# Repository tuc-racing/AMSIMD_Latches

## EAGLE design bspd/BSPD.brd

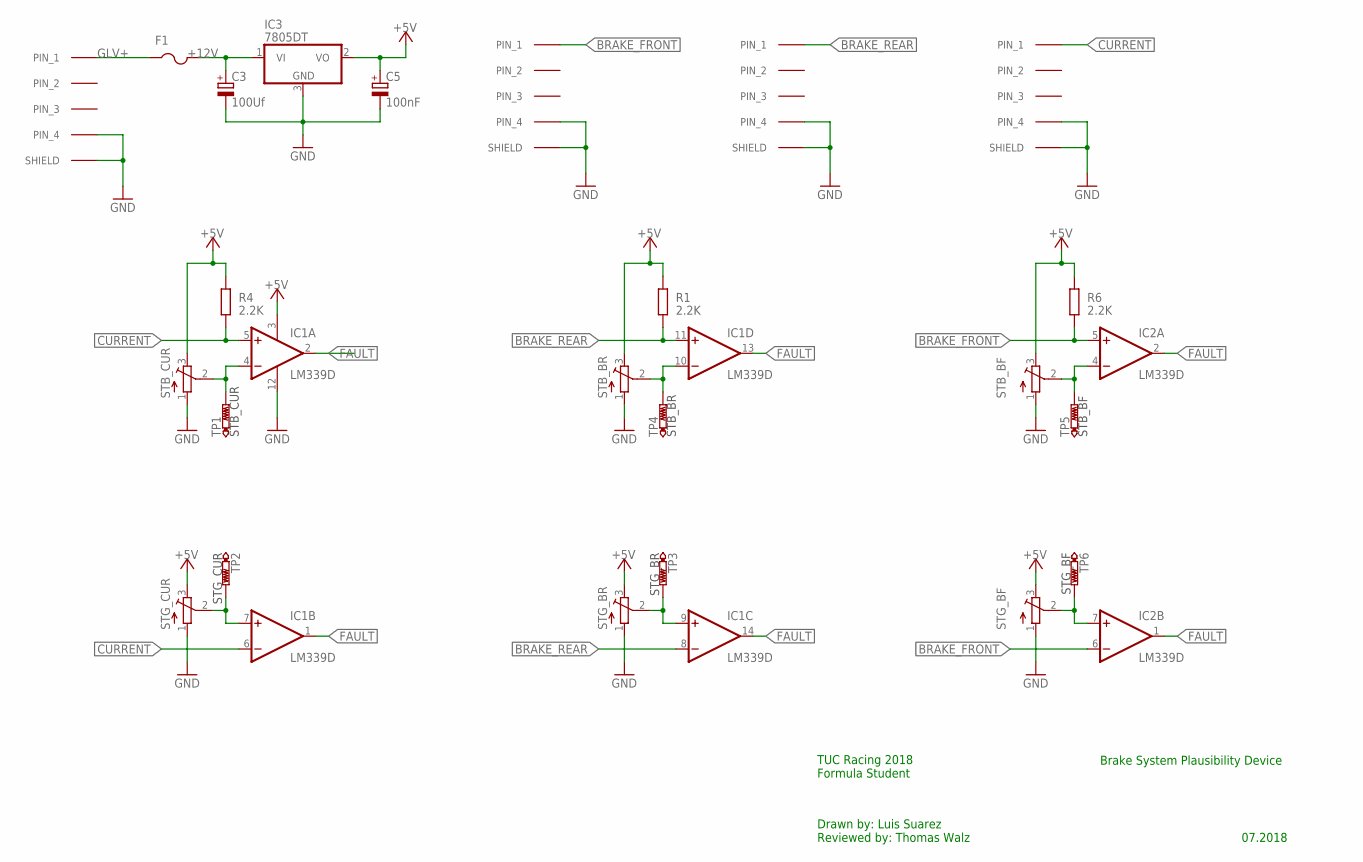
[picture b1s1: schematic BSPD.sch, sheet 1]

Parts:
C3: 100Uf; PANASONIC_D
C5: 100nF; PANASONIC_C
F1: PTCFUSE-1206; R1206
IC1, IC2: LM339D; SO14
IC3: 7805DT; TO252
POWER, POWER1, POWER2, POWER3: M8-718-MALE; M18-718-MALE
R1, R4, R6: 2.2K; R0805
STB_BF: TRIM_EU-SM-42/43B; SM-42/43B
STB_BR: TRIM_EU-SM-42/43B; SM-42/43B
STB_CUR: TRIM_EU-SM-42/43B; SM-42/43B
STG_BF: TRIM_EU-SM-42/43B; SM-42/43B
STG_BR: TRIM_EU-SM-42/43B; SM-42/43B
STG_CUR: TRIM_EU-SM-42/43B; SM-42/43B
TP1, TP2, TP3, TP4, TP5, TP6: PTR1PAD1-13; P1-13

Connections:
+5V: C5.+, IC1.3 (V+), IC3.2 (VO), R1.2, R4.2, R6.2, STB_BF.3 (E), STB_BR.3 (E), STB_CUR.3 (E), STG_BF.3 (E), STG_BR.3 (E), STG_CUR.3 (E); also elsewhere on the board
+12V: C3.+, F1.2, IC3.1 (VI)
BRAKE_FRONT: IC2.5 (+IN), IC2.6 (-IN), POWER1.P$1 (PIN_1), R6.1
BRAKE_REAR: IC1.8 (-IN), IC1.11 (+IN), POWER2.P$1 (PIN_1), R1.1
CURRENT: IC1.5 (+IN), IC1.6 (-IN), POWER3.P$1 (PIN_1), R4.1
FAULT: IC1.1 (OUT), IC1.2 (OUT), IC1.13 (OUT), IC1.14 (OUT), IC2.1 (OUT), IC2.2 (OUT); also elsewhere on the board
GLV+: F1.1, POWER.P$1 (PIN_1); also elsewhere on the board
GND: C3.-, C5.-, IC1.12 (GND), IC3.3 (GND), POWER.L (SHIELD), POWER.P$4 (PIN_4), POWER.R (SHIELD), POWER1.L (SHIELD), POWER1.P$4 (PIN_4), POWER1.R (SHIELD), POWER2.L (SHIELD), POWER2.P$4 (PIN_4), POWER2.R (SHIELD), POWER3.L (SHIELD), POWER3.P$4 (PIN_4), POWER3.R (SHIELD), STB_BF.1 (A), STB_BR.1 (A), STB_CUR.1 (A), STG_BF.1 (A), STG_BR.1 (A), STG_CUR.1 (A); also elsewhere on the board
STB_BF_TH: IC2.4 (-IN), STB_BF.2 (S), TP5.TP
STB_BR_TH: IC1.10 (-IN), STB_BR.2 (S), TP4.TP
STB_CUR_TH: IC1.4 (-IN), STB_CUR.2 (S), TP1.TP
STG_BR_TH: IC1.9 (+IN), STG_BR.2 (S), TP3.TP
STG_CUR_TH: IC1.7 (+IN), STG_CUR.2 (S), TP2.TP
TP_STG_BF: IC2.7 (+IN), STG_BF.2 (S), TP6.TP

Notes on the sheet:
Brake System Plausibility Device
07.2018
Drawn by: Luis Suarez Reviewed by: Thomas Walz
TUC Racing 2018 Formula Student

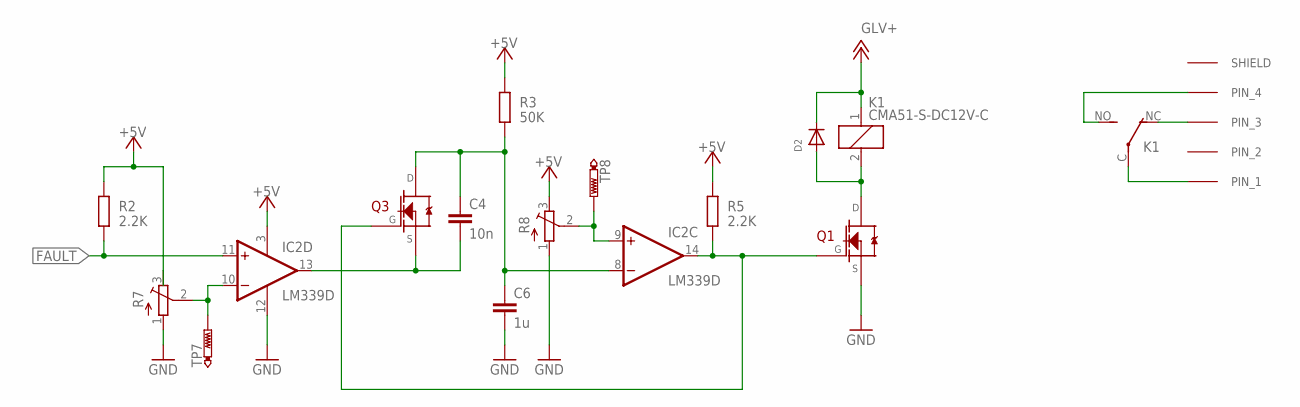
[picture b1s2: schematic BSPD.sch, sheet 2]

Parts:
C4: 10n; C1210
C6: 1u; C1210
D2: DIODESOD-123; SOD-123
IC2: LM339D; SO14
K1: CMA51-S-DC12V-C; CQ1
Q1, Q3: INF-PG-TDSON-8-1_V_1; INF-PG-TDSON-8-1_V_1PRIMARY
R2, R5: 2.2K; R0805
R3: 50K; R0805
R7, R8: TRIM_EU-SM-42/43B; SM-42/43B
TP7, TP8: PTR1PAD1-13; P1-13
U$1: M8-718-MALE; M18-718-MALE

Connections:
+5V: IC2.3 (V+), R2.2, R3.2, R5.2, R7.3 (E), R8.3 (E); also elsewhere on the board
BSPD+: K1.NO (S), U$1.P$4 (PIN_4)
BSPD-: K1.C, U$1.P$1 (PIN_1)
FAULT: IC2.11 (+IN), R2.1; also elsewhere on the board
FAULT_STATE: C4.2, IC2.13 (OUT), Q3.1 (S), Q3.2 (S), Q3.3 (S)
GLV+: D2.C, K1.1; also elsewhere on the board
GND: C6.2, IC2.12 (GND), Q1.1 (S), Q1.2 (S), Q1.3 (S), R7.1 (A), R8.1 (A); also elsewhere on the board
unnamed: D2.A, K1.2, Q1.5 (D), Q1.6 (D), Q1.7 (D), Q1.8 (D)
unnamed: K1.NC (O), U$1.P$3 (PIN_3)
unnamed: IC2.10 (-IN), R7.2 (S), TP7.TP
unnamed: IC2.9 (+IN), R8.2 (S), TP8.TP
unnamed: C4.1, C6.1, IC2.8 (-IN), Q3.5 (D), Q3.6 (D), Q3.7 (D), Q3.8 (D), R3.1
OUT_STATUS: IC2.14 (OUT), Q1.4 (G), Q3.4 (G), R5.1

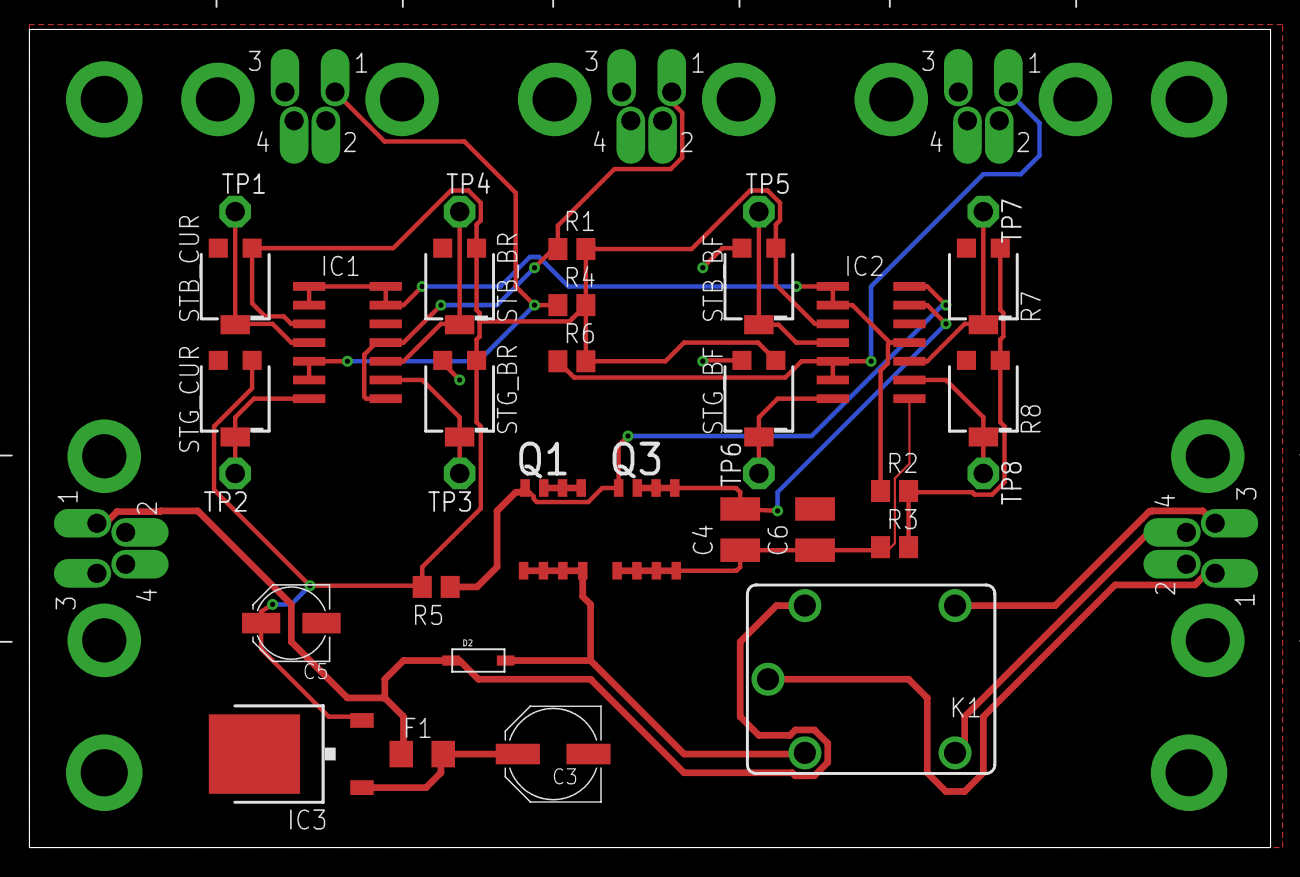
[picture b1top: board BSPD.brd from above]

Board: 2 copper layers, 84.3 x 55.5 mm, 39 parts (0 on the bottom side), 23 nets.

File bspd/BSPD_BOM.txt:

Stückliste exportiert aus C:/Users/Sean/OneDrive/Documents/T.U.C-Racing/Git_V2/hardware/bspd/BSPD.sch am 04.03.2018 19:50

Part    Value           Device               Package                     Description                                   LABEL       MF MPN OC_FARNELL OC_NEWARK TP_SIGNAL_NAME
C3      100Uf           CPOL-EUD             PANASONIC_D                 POLARIZED CAPACITOR, European symbol                                                                
C4      10n             C-EUC1210            C1210                       CAPACITOR, European symbol                                                                          
C5      100nF           CPOL-EUC             PANASONIC_C                 POLARIZED CAPACITOR, European symbol                                                                
C6      1u              C-EUC1210            C1210                       CAPACITOR, European symbol                                                                          
D2                      DIODESOD-123         SOD-123                     Diode                                                                                               
F1                      PTCFUSE-1206         R1206                       PTC fuses, resettable thermistors                                                                   
IC1     LM339D          LM339D               SO14                        Low Power Low Offset Voltage Quad Comparators                                                       
IC2     LM339D          LM339D               SO14                        Low Power Low Offset Voltage Quad Comparators                                                       
IC3     7805DT          7805DT               TO252                       Positive VOLTAGE REGULATOR                                                                          
K1      CMA51-S-DC12V-C CQ1-12V              CQ1                         AUTOMOTIVE QUIET RELAY NAiS                                      unknown    unknown                 
POWER   M8-718-MALE     M8-718-MALE          M18-718-MALE                                                              POWER                                                 
POWER1  M8-718-MALE     M8-718-MALE          M18-718-MALE                                                              BRAKE_FRONT                                           
POWER2  M8-718-MALE     M8-718-MALE          M18-718-MALE                                                              BRAKE_REAR                                            
POWER3  M8-718-MALE     M8-718-MALE          M18-718-MALE                                                              CURRENT                                               
Q1                      INF-PG-TDSON-8-1_V_1 INF-PG-TDSON-8-1_V_1PRIMARY                                                                                                     
Q3                      INF-PG-TDSON-8-1_V_1 INF-PG-TDSON-8-1_V_1PRIMARY                                                                                                     
R1      2.2K            R-EU_R0805           R0805                       RESISTOR, European symbol                                                                           
R2      2.2K            R-EU_R0805           R0805                       RESISTOR, European symbol                                                                           
R3      50K             R-EU_R0805           R0805                       RESISTOR, European symbol                                                                           
R4      2.2K            R-EU_R0805           R0805                       RESISTOR, European symbol                                                                           
R5      2.2K            R-EU_R0805           R0805                       RESISTOR, European symbol                                                                           
R6      2.2K            R-EU_R0805           R0805                       RESISTOR, European symbol                                                                           
R7                      TRIM_EU-SM-42/43B    SM-42/43B                   POTENTIOMETER                                                                                       
R8                      TRIM_EU-SM-42/43B    SM-42/43B                   POTENTIOMETER                                                                                       
STB_BF                  TRIM_EU-SM-42/43B    SM-42/43B                   POTENTIOMETER                                                                                       
STB_BR                  TRIM_EU-SM-42/43B    SM-42/43B                   POTENTIOMETER                                                                                       
STB_CUR                 TRIM_EU-SM-42/43B    SM-42/43B                   POTENTIOMETER                                                                                       
STG_BF                  TRIM_EU-SM-42/43B    SM-42/43B                   POTENTIOMETER                                                                                       
STG_BR                  TRIM_EU-SM-42/43B    SM-42/43B                   POTENTIOMETER                                                                                       
STG_CUR                 TRIM_EU-SM-42/43B    SM-42/43B                   POTENTIOMETER                                                                                       
TP1     PTR1PAD1-13     PTR1PAD1-13          P1-13                       TEST PIN                                                                              STB_CUR       
TP2     PTR1PAD1-13     PTR1PAD1-13          P1-13                       TEST PIN                                                                              STG_CUR       
TP3     PTR1PAD1-13     PTR1PAD1-13          P1-13                       TEST PIN                                                                              STG_BR        
TP4     PTR1PAD1-13     PTR1PAD1-13          P1-13                       TEST PIN                                                                              STB_BR        
TP5     PTR1PAD1-13     PTR1PAD1-13          P1-13                       TEST PIN                                                                              STB_BF        
TP6     PTR1PAD1-13     PTR1PAD1-13          P1-13                       TEST PIN                                                                              STG_BF        
TP7     PTR1PAD1-13     PTR1PAD1-13          P1-13                       TEST PIN                                                                                            
TP8     PTR1PAD1-13     PTR1PAD1-13          P1-13                       TEST PIN                                                                                            
U$1     M8-718-MALE     M8-718-MALE          M18-718-MALE                                                              OUTPUT

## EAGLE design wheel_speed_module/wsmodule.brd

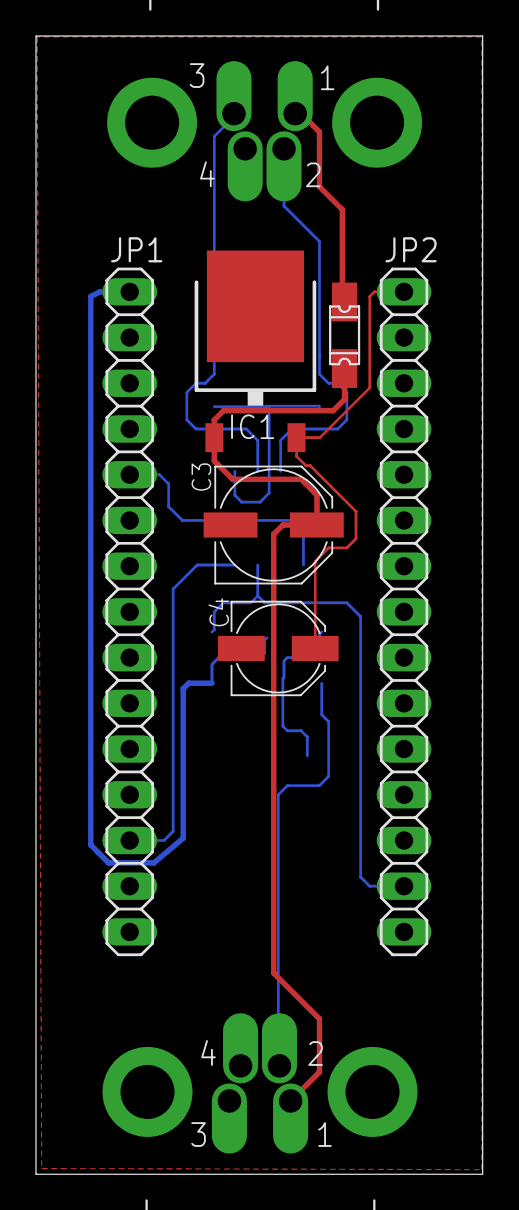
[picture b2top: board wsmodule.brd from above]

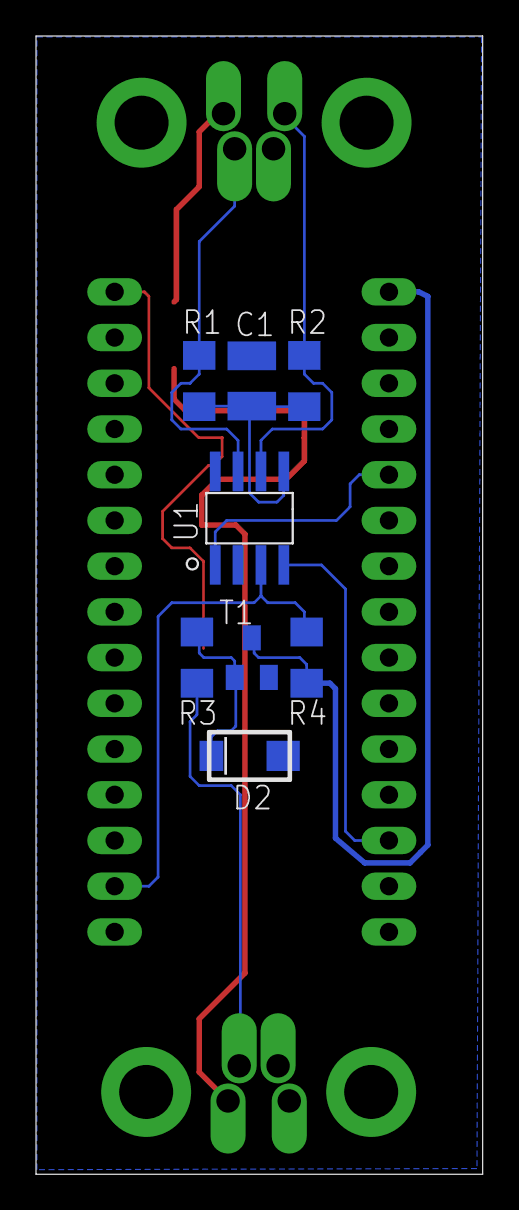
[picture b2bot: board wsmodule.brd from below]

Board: 2 copper layers, 24.8 x 63.2 mm, 16 parts (8 on the bottom side), 13 nets.

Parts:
C1: 47u; C1210
C3: 100uF; PANASONIC_D
C4: 10uF; PANASONIC_C
D2: GF1
F1: 1206L
IC1: 7805DT; TO252
INPUT: M8-718-MALE; M18-718-MALE
JP1, JP2: 1X15
OUTPUT: M8-718-FEMALE; M18-718-FEMALE
R1, R2: 60; R1206
R3, R4: 10K; R1206
T1: SOT23
U1: LTC2875XS; SO-08

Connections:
3V3: JP2.14, R4.2, U1.3
5V: C4.+, IC1.2, JP2.1
CANH: INPUT.P$2, R1.2, U1.7
CANL: INPUT.P$3, R2.2, U1.6
CAN_RX: JP1.13, U1.4
CAN_TX: JP1.5, U1.1
DIN1: JP1.1, R4.1, T1.3
GND: C1.2, C3.-, C4.-, D2.A, IC1.3, INPUT.L, INPUT.P$4, INPUT.R, JP2.2, JP2.12, OUTPUT.L, OUTPUT.P$4, OUTPUT.R, T1.2, U1.2, U1.8
HALL1: OUTPUT.P$2, R3.1
unnamed: D2.C, R3.2, T1.1
unnamed: C1.1, R1.1, R2.1, U1.5
VCC: F1.P$2, INPUT.P$1
VIN: C3.+, F1.P$1, IC1.1, OUTPUT.P$1

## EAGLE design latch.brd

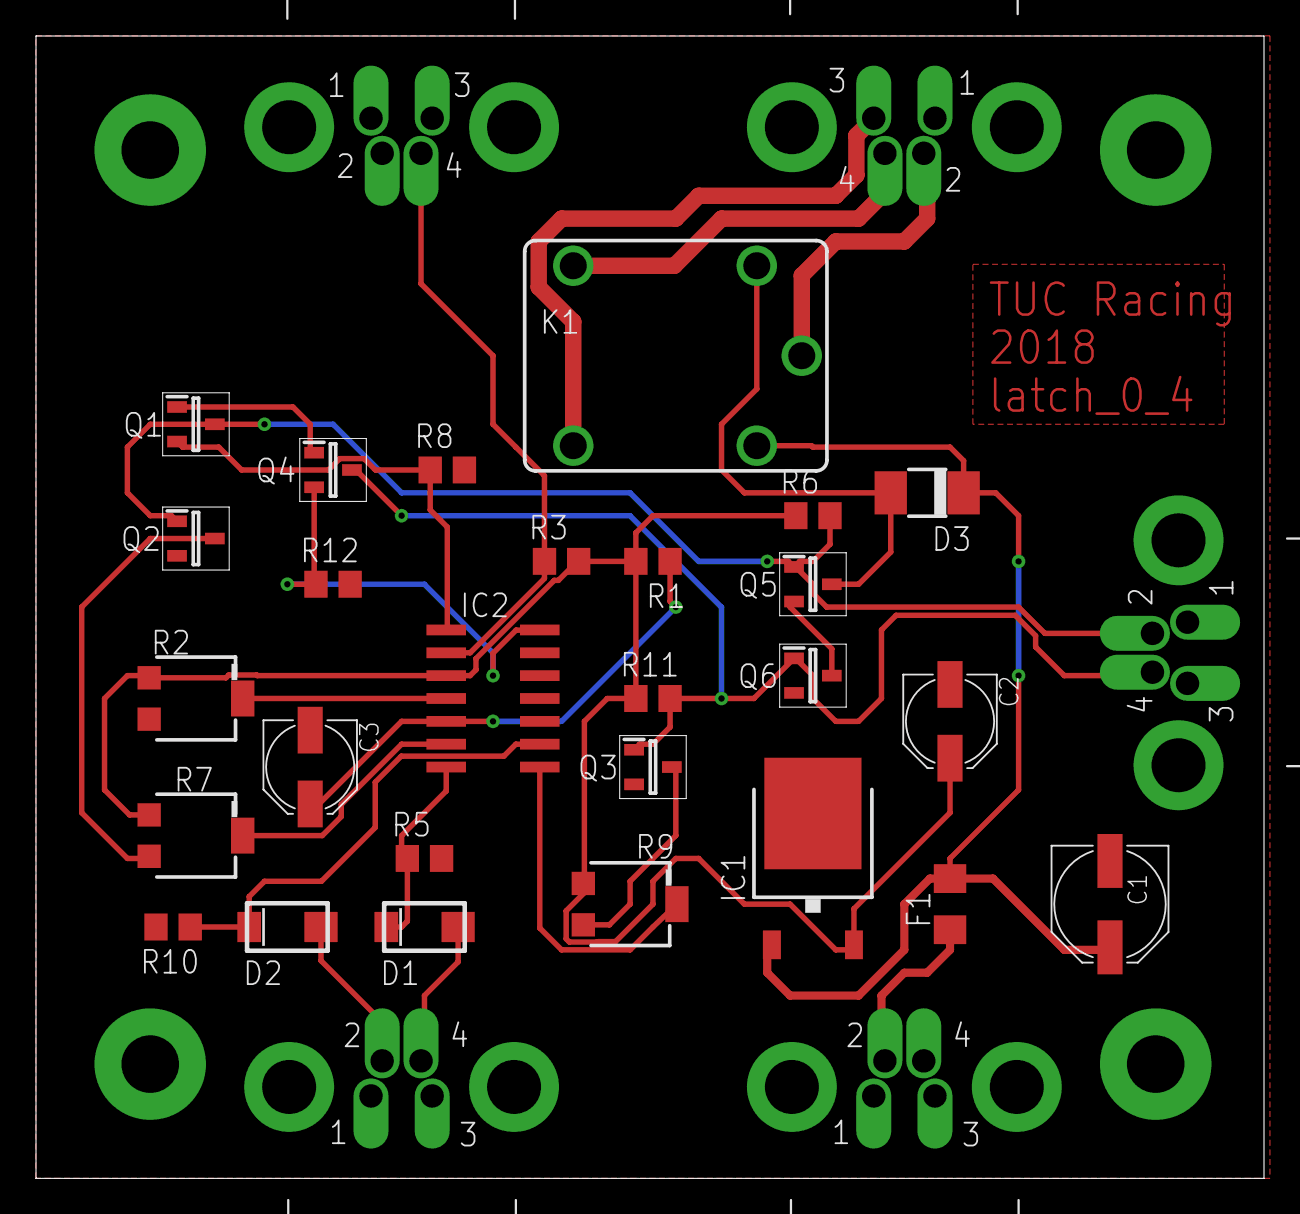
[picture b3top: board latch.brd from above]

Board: 2 copper layers, 68.2 x 63.5 mm, 32 parts (0 on the bottom side), 25 nets.

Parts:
C1: 100uF; PANASONIC_D
C2, C3: 10uF; PANASONIC_C
D1, D2: 1N4148; GF1
D3: 1N4148; DO-214AC
F1: 1A; R1206
IC1: 7805DT; TO252
IC2: LM339D; SO14
INDICATORS: M8-718-FEMALE; M18-718-FEMALE
K1: CMA51-S-DC12V-C; CQ1
LATCH: M8-718-MALE; M18-718-MALE
POWER_CONN: POWER; M18-718-MALE
Q1, Q2, Q3, Q4, Q5, Q6: BS170; SOT96P240X100-3N
R1, R8, R12: 100K; R0805
R2, R7, R9: 12K; SM-42/43B
R3, R6, R11: 1K; R0805
R5, R10: 2.2K; R0805
RESET: M8-718-FEMALE; M18-718-FEMALE
STATUS: M8-718-MALE; M18-718-MALE

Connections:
+5V: C2.+, IC1.2, IC2.3, R1.2, R2.3, R3.2, R6.2, R7.3, R9.3, R11.2
+12V: C1.+, D3.C, F1.2, IC1.1, K1.1
AMS_FAIL: INDICATORS.P$4, Q3.1, Q4.3, Q6.1, R11.1
AMS_STATUS: D2.A, STATUS.P$2
DELAY_PWR: Q1.1, Q4.1
DELAY_RESET: IC2.2, R3.1, RESET.P$4
GLV+: F1.1, POWER_CONN.P$2
GND: C1.-, C2.-, C3.-, IC1.3, IC2.10, IC2.11, IC2.12, INDICATORS.L, INDICATORS.P$1, INDICATORS.P$3, INDICATORS.R, POWER_CONN.L, POWER_CONN.P$4, POWER_CONN.R, Q2.2, Q3.2, Q6.2, R2.1, R5.1, R8.1, R10.1, R12.1, RESET.L, RESET.P$2, RESET.R, STATUS.L, STATUS.P$1, STATUS.P$3, STATUS.R
IMD_FAIL: INDICATORS.P$2, Q1.3, Q2.1, Q5.1, R6.1
IMD_STATUS: D1.A, STATUS.P$4
LATCH+: K1.NO, LATCH.P$4
LATCH-: K1.C, LATCH.P$2
unnamed: IC2.4, R2.2
unnamed: C3.+, IC2.5, R1.1
unnamed: D1.C, IC2.7, R5.2
unnamed: IC2.6, R7.2
unnamed: Q2.3, R7.1
unnamed: D2.C, IC2.9, R10.2
unnamed: IC2.1, Q1.2, R8.2
unnamed: IC2.8, R9.2
unnamed: Q3.3, R9.1
unnamed: IC2.14, Q4.2, R12.2
unnamed: D3.A, K1.2, Q5.3
unnamed: Q5.2, Q6.3
unnamed: K1.NC, LATCH.P$3

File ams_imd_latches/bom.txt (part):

Stückliste exportiert aus C:/Users/Sean/OneDrive/Documents/T.U.C-Racing/Git_V2/hardware/ams_imd_latches/latch.sch am 12.02.2018 21:47

Part       Value           Device            Package          Description                                                                                                        3D_PACKAGE ALLIED_NUMBER DESCRIPTION                                                                                                        HEIGHT MANUFACTURER_NAME MANUFACTURER_PART_NUMBER MF MPN OC_FARNELL OC_NEWARK OTHER_PART_NUMBER RS_PART_NUMBER SUPPLIER_NAME
C1         100uF           CPOL-EUD          PANASONIC_D      POLARIZED CAPACITOR, European symbol                                                                                                                                                                                                                                                                                                                                                       
C2         10uF            CPOL-EUC          PANASONIC_C      POLARIZED CAPACITOR, European symbol                                                                                                                                                                                                                                                                                                                                                       
C3         10uF            CPOL-EUC          PANASONIC_C      POLARIZED CAPACITOR, European symbol                                                                                                                                                                                                                                                                                                                                                       
D1         1N4148          DIODE-GF1         GF1              DIODE                                                                                                                                                                                                                                                                                                                                                                                      
D2         1N4148          DIODE-GF1         GF1              DIODE                                                                                                                                                                                                                                                                                                                                                                                      
D3         1N4148          DIODE-DO-214AC    DO-214AC         DIODE                                                                                                                                                                                                                                                                                                                                                                                      
F1         1A              PTCFUSE-1206      R1206            PTC fuses, resettable thermistors                                                                                                                                                                                                                                                                                                                                                          
IC1        7805DT          7805DT            TO252            Positive VOLTAGE REGULATOR                                                                                                                                                                                                                                                                                                                                                                 
IC2        LM339D          LM339D            SO14             Low Power Low Offset Voltage Quad Comparators                                                                                                                                                                                                                                                                                                                                              
INDICATORS M8-718-FEMALE   M8-718-FEMALE     M18-718-FEMALE                                                                                                                                                                                                                                                                                                                                                                                              
K1         CMA51-S-DC12V-C CQ1-12V           CQ1              AUTOMOTIVE QUIET RELAY NAiS                                                                                                                                                                                                                                                                                             unknown    unknown                                                 
LATCH      M8-718-MALE     M8-718-MALE       M18-718-MALE                                                                                                                                                                                                                                                                                                                                                                                                
POWER_CONN POWER           M8-718-MALE       M18-718-MALE                                                                                                                                                                                                                                                                                                                                                                                                
Q1         BS170           BS170FTA          SOT96P240X100-3N MOSFET N-Channel 60V 0.00015A SOT23 Diodes Inc BS170FTA N-channel MOSFET Transistor, 0.00015 A, 60 V, 3-Pin SOT-23                          MOSFET N-Channel 60V 0.00015A SOT23 Diodes Inc BS170FTA N-channel MOSFET Transistor, 0.00015 A, 60 V, 3-Pin SOT-23 1mm    Diodes Inc.       BS170FTA                                                               2156587P       RS           
Q2         BS170           BS170FTA          SOT96P240X100-3N MOSFET N-Channel 60V 0.00015A SOT23 Diodes Inc BS170FTA N-channel MOSFET Transistor, 0.00015 A, 60 V, 3-Pin SOT-23                          MOSFET N-Channel 60V 0.00015A SOT23 Diodes Inc BS170FTA N-channel MOSFET Transistor, 0.00015 A, 60 V, 3-Pin SOT-23 1mm    Diodes Inc.       BS170FTA                                                               2156587P       RS           
Q3         BS170           BS170FTA          SOT96P240X100-3N MOSFET N-Channel 60V 0.00015A SOT23 Diodes Inc BS170FTA N-channel MOSFET Transistor, 0.00015 A, 60 V, 3-Pin SOT-23                          MOSFET N-Channel 60V 0.00015A SOT23 Diodes Inc BS170FTA N-channel MOSFET Transistor, 0.00015 A, 60 V, 3-Pin SOT-23 1mm    Diodes Inc.       BS170FTA                                                               2156587P       RS           
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
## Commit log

2018-02-05 First version of latches board
2018-02-05 Second version of latches board
2018-02-05 Third version of latches board
2018-02-05 Add board design for fourth version
2018-02-06 Changed directory structure
    Moved
2018-02-06 First implementation of Wheel Speed Sensor module
    First version single sided.
2018-02-06 Version 1.1
2018-02-06 Version 1.2
2018-02-06 Version 1.3
    Two sided assembly. New M8 connectors at each end.
2018-02-08 First version of BSPD 2018
2018-02-12 Added BOM
2018-02-12 Add PDF for schematic
2018-02-17 Added review document
    Let me know if this isn´t what you had in mind or if I forgot to check something.
2018-02-17 Added review document
    Let me know if I missed anything
2018-03-04 Changes to review document
2018-03-04 Added BSPD BOM and review document
